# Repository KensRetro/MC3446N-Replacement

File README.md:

A replacement for the no longer manufactured MC3446 IC.  Not exactly the same spec but unless you are loading it down with many connections you'll never notice.

The module is simple and most of the time fits right into the socket if there's enough clearance.
The circuit mimics the internals of the original chip and has been tested in a PET computer with great success.

Very few parts needed to assemble the board.  It is recommended to mount the board at the TOP of the pins (or shear off the pins) so the 
surface mount components will sit correctly.  Minimal surface mount soldering is needed, a little care and patience goes a long way.

DISCLAIMER: All information is provided 'AS-IS" for informational purposes only. I have tried to be as accurate as possible but that doesn't mean there are no mistakes. Any errors or omissions etc. are your own responsibility.
There is no Warranty or guarantee of any kind. See licence for details.

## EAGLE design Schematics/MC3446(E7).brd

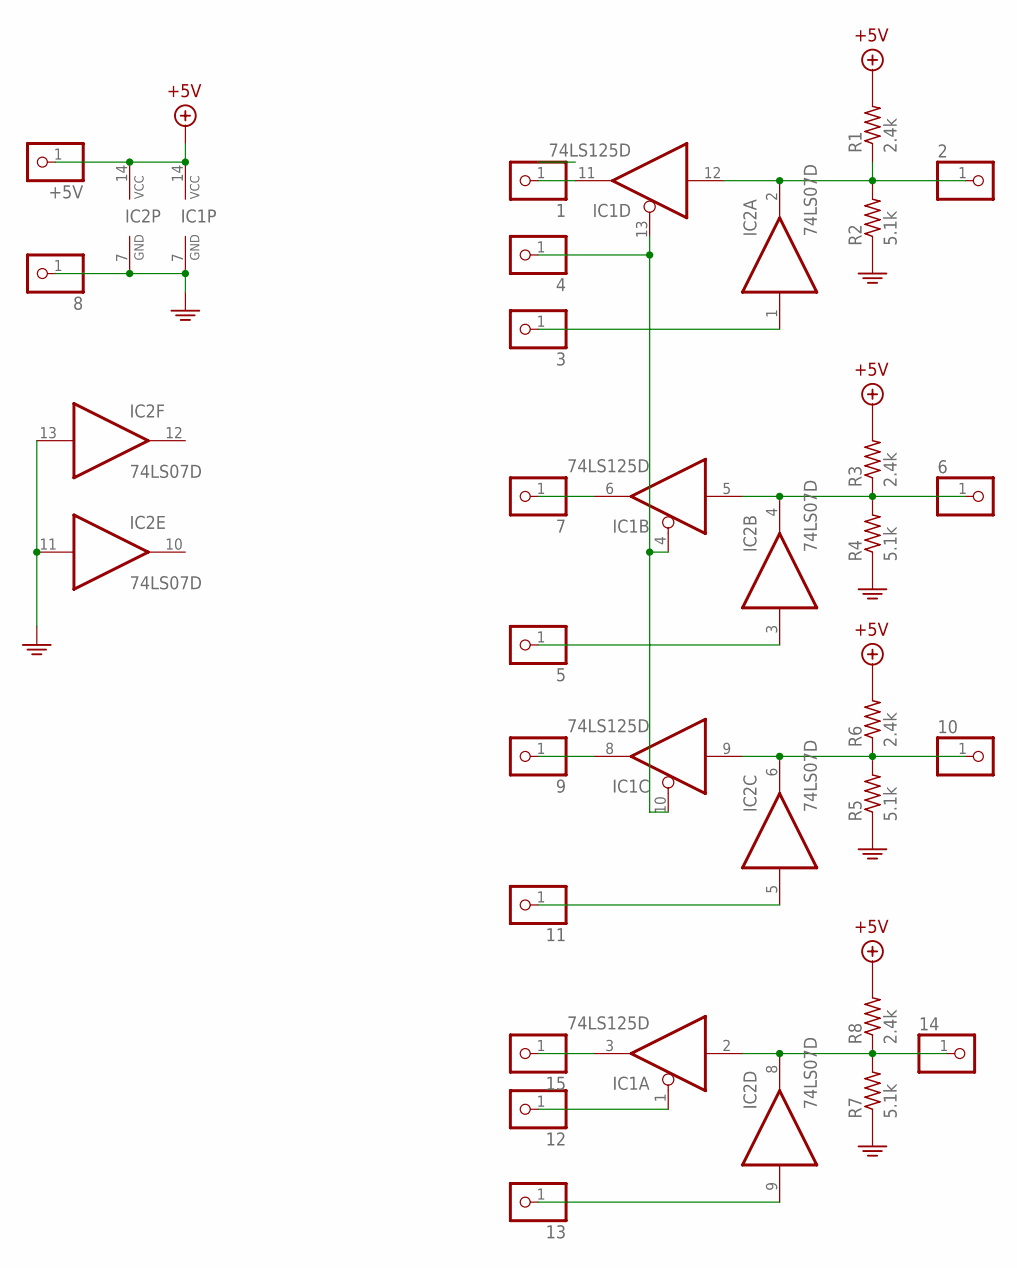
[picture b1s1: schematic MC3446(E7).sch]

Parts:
1, 2, 3, 4, 5, 6, 7, 8, 9, 10, 11, 12, 13, 14, 15: PINHD-1X1; 1X01
+5V: PINHD-1X1; 1X01
IC1: 74LS125D; SO14
IC2: 74LS07D; SO14
R1, R3, R6, R8: 2.4k; R0805
R2, R4, R5, R7: 5.1k; R0805

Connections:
+5V: +5V.1, IC1.14 (VCC), IC2.14 (VCC), R1.2, R3.2, R6.2, R8.2
GND: 8.1, IC1.7 (GND), IC2.7 (GND), IC2.11 (I), IC2.13 (I), R2.1, R4.1, R5.1, R7.1
unnamed: 2.1, IC1.12 (I), IC2.2 (O), R1.1, R2.2
unnamed: 3.1, IC2.1 (I)
unnamed: 1.1, IC1.11 (O)
unnamed: 4.1, IC1.4 (OE), IC1.10 (OE), IC1.13 (OE)
unnamed: 6.1, IC1.5 (I), IC2.4 (O), R3.1, R4.2
unnamed: 10.1, IC1.9 (I), IC2.6 (O), R5.2, R6.1
unnamed: 14.1, IC1.2 (I), IC2.8 (O), R7.2, R8.1
unnamed: 7.1, IC1.6 (O)
unnamed: 5.1, IC2.3 (I)
unnamed: 9.1, IC1.8 (O)
unnamed: 15.1, IC1.3 (O)
unnamed: 11.1, IC2.5 (I)
unnamed: 13.1, IC2.9 (I)
unnamed: 12.1, IC1.1 (OE)

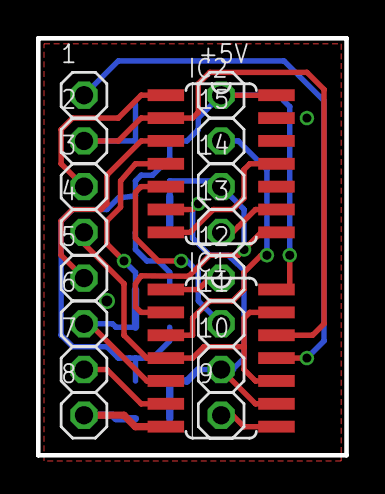
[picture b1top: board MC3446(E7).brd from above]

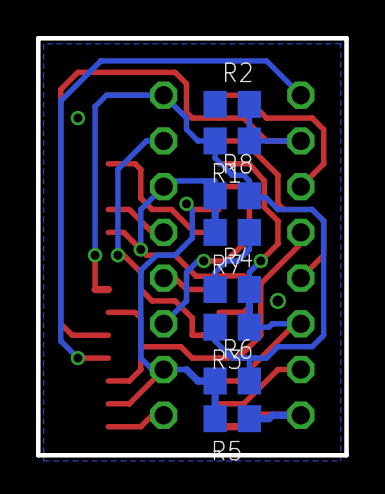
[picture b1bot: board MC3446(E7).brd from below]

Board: 2 copper layers, 17.1 x 23.2 mm, 26 parts (8 on the bottom side), 16 nets.

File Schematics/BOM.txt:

Qty Value    Device     Parts                                                 
16           PINHD-1X1  +5V, 1, 2, 3, 4, 5, 6, 7, 8, 9, 10, 11, 12, 13, 14, 15
4   2.4k     R-US_R0805 R1, R3, R6, R8                                        
4   5.1k     R-US_R0805 R2, R4, R5, R7                                        
1   74LS07D  74LS07D    IC2                                                   
1   74LS125D 74LS125D   IC1
